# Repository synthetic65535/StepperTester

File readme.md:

# StepperTester
Simple stepper motor tester.

* Based on pololu stepper driver and 555 timer
* No microcontrollers
* Only through-hole components
* Single sided PCB, DIY-frendly.
* IDE: KiCad 4.0.7

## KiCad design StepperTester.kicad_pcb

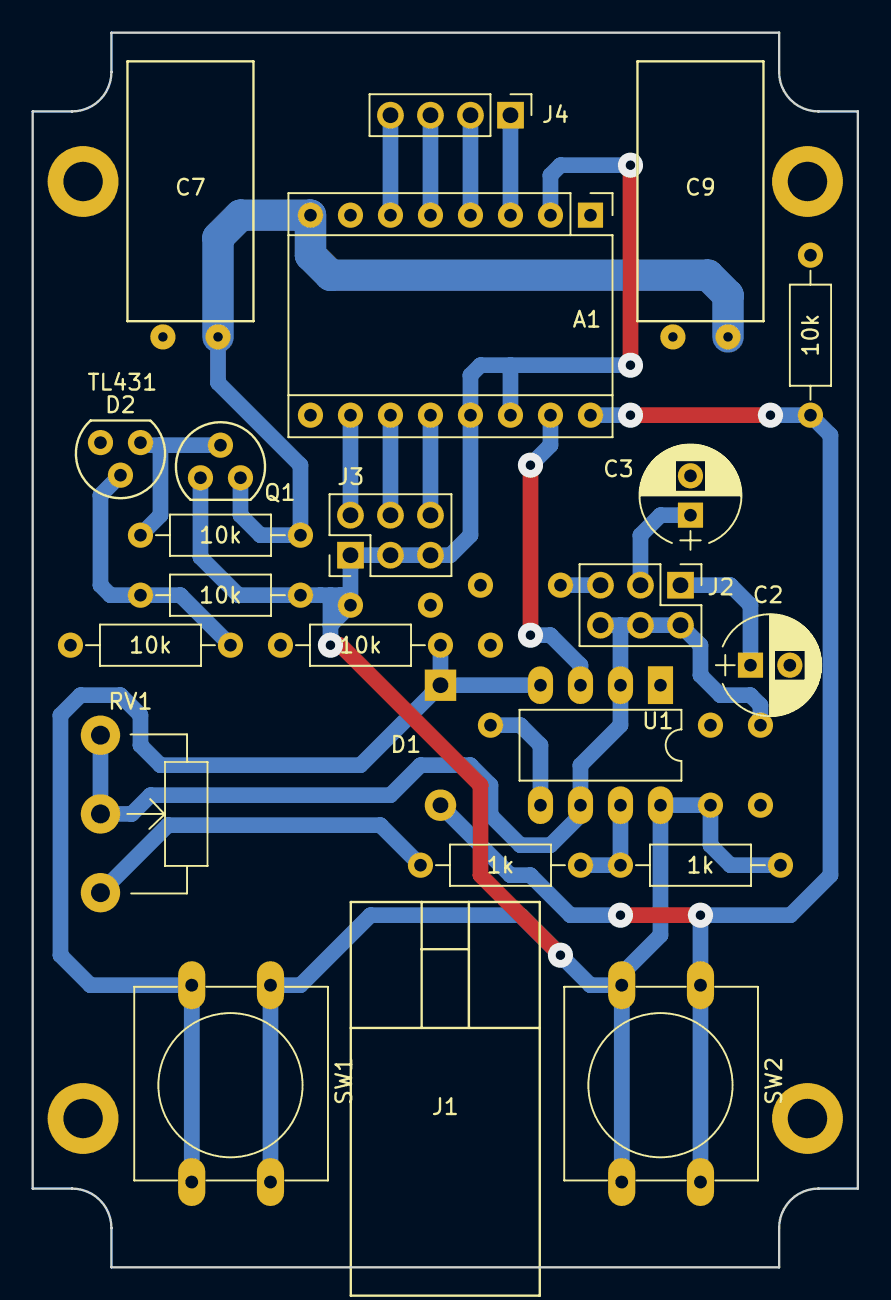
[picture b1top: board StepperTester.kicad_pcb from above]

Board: 2 copper layers, 52.4 x 78.4 mm, 28 parts (0 on the bottom side), 22 nets.

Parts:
A1: Driver_Motor:Pololu_Breakout_A4988; Pololu_Breakout-16_15.2x20.3mm
C1, C5, C6, C8: 100nF; CAP
C2: 100uF; CP_Radial_D6.3mm_P2.50mm
C3: 10uF; CP_Radial_D6.3mm_P2.50mm
C4: 1uF; CAP
C7, C9: 1000uF; Capacitor_THT_Radial_D8_L16.5_P3.5_Horizontal
D1: D_Schottky_ALT; DO-41
D2: TL431
J1: DS-025A
J2, J3: Conn_02x03_Odd_Even; Pin_Header_Straight_2x03_Pitch2.54mm
J4: Conn_01x04; Pin_Header_Straight_1x04_Pitch2.54mm
Q1: PN2222A; Q_EBC
R1, R2: 1k; RES
R3, R4, R5, R6, R7: 10k; RES
RV1: 10k; Potentiometer_WirePads
SW1, SW2: SW_Push; SW_PUSH-12mm
U1: NE555; DIP-8_W7.62mm_LongPads

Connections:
+5V: A1.2, A1.13, A1.14, C1.1, C8.1, J3.1, J3.3, J3.5, Q1.1, R1.1, R6.2, SW1.1, SW2.2, U1.8
+24V: A1.8, C7.1, C9.1, Q1.3, R5.2
DIR: A1.16, D1.2, R4.2, SW2.1
GNDD: A1.1, A1.7, A1.9, C1.2, C2.2, C3.2, C4.2, C5.2, C6.2, C7.2, C8.2, C9.2, D2.3, J1.2, R3.1, R4.1, R7.1, U1.1
unnamed: A1.3, J4.1
unnamed: A1.4, J4.2
unnamed: A1.5, J4.3
unnamed: A1.6, J4.4
unnamed: A1.10, J3.2
unnamed: A1.11, J3.4
unnamed: A1.12, J3.6
unnamed: A1.15, U1.3
unnamed: C2.1, J2.1
unnamed: C3.1, J2.3
unnamed: C4.1, J2.5
unnamed: C5.1, J2.2, J2.4, J2.6, RV1.1, RV1.2, U1.2, U1.6
unnamed: C6.1, U1.5
unnamed: D2.1, Q1.2, R5.1
unnamed: D2.2, R6.1, R7.2
unnamed: R1.2, R2.1, U1.7
unnamed: R2.2, RV1.3
~RESET: D1.1, R3.2, SW1.2, U1.4
